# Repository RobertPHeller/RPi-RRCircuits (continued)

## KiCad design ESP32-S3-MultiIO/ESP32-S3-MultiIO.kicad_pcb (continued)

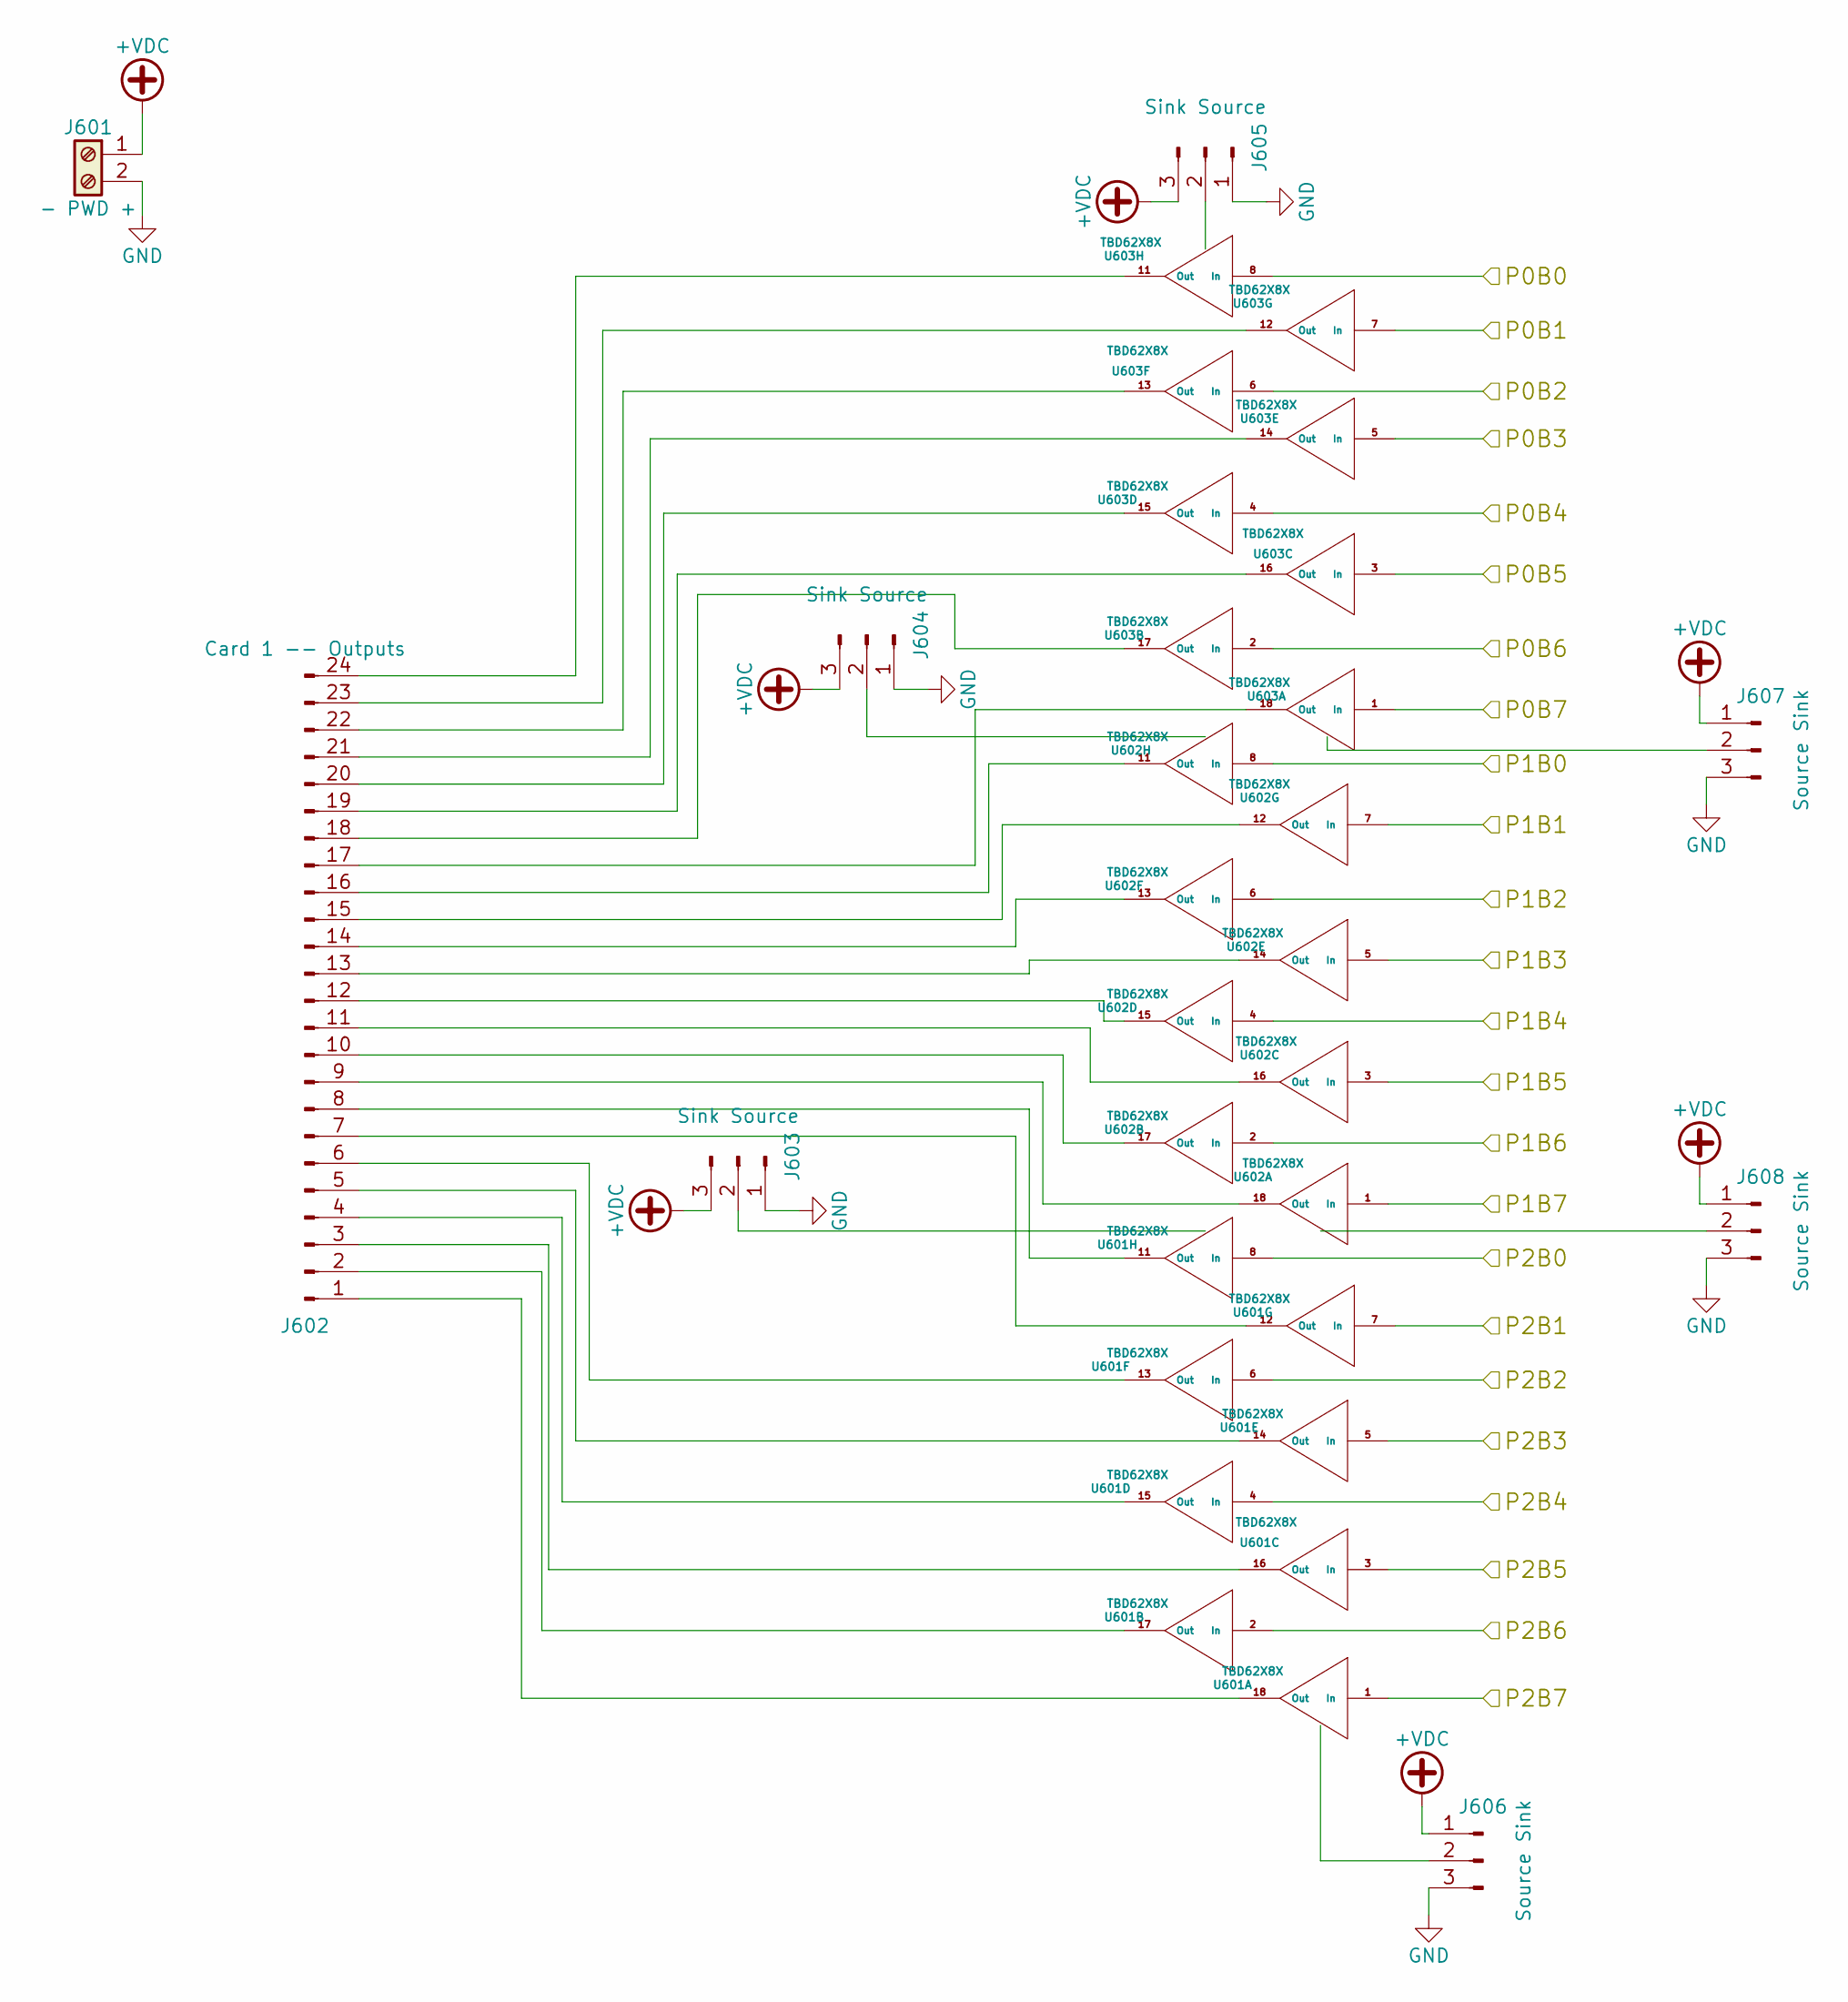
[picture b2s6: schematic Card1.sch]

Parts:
J601: - PWD +; TerminalBlock_Pheonix_MPT-2.54mm_2pol
J602: Card 1 -- Outputs; Molex_KK_396_01x24_3.96mm_RightAngle; Mouser Part Number 538-26-48-1242
J603, J604, J605: Sink Source; Pin_Header_Straight_1x03_Pitch2.54mm
J606, J607, J608: Source Sink; Pin_Header_Straight_1x03_Pitch2.54mm
U601, U602, U603: TBD62X8X; DIP-18_W7.62mm; Mouser Part Number 571-1-2199298-5

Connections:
+VDC: J601.1, J603.3, J604.3, J605.3, J606.1, J607.1, J608.1; also elsewhere on the board
/MCU/C1A0: U603.8 (In); also elsewhere on the board
/MCU/C1A1: U603.7 (In); also elsewhere on the board
/MCU/C1A2: U603.6 (In); also elsewhere on the board
/MCU/C1A3: U603.5 (In); also elsewhere on the board
/MCU/C1A4: U603.4 (In); also elsewhere on the board
/MCU/C1A5: U603.3 (In); also elsewhere on the board
/MCU/C1A6: U603.2 (In); also elsewhere on the board
/MCU/C1A7: U603.1 (In); also elsewhere on the board
/MCU/C1B0: U602.8 (In); also elsewhere on the board
/MCU/C1B1: U602.7 (In); also elsewhere on the board
/MCU/C1B2: U602.6 (In); also elsewhere on the board
/MCU/C1B3: U602.5 (In); also elsewhere on the board
/MCU/C1B4: U602.4 (In); also elsewhere on the board
/MCU/C1B5: U602.3 (In); also elsewhere on the board
/MCU/C1B6: U602.2 (In); also elsewhere on the board
/MCU/C1B7: U602.1 (In); also elsewhere on the board
/MCU/C1C0: U601.8 (In); also elsewhere on the board
/MCU/C1C1: U601.7 (In); also elsewhere on the board
/MCU/C1C2: U601.6 (In); also elsewhere on the board
/MCU/C1C3: U601.5 (In); also elsewhere on the board
/MCU/C1C4: U601.4 (In); also elsewhere on the board
/MCU/C1C5: U601.3 (In); also elsewhere on the board
/MCU/C1C6: U601.2 (In); also elsewhere on the board
/MCU/C1C7: U601.1 (In); also elsewhere on the board
GND: J601.2, J603.1, J604.1, J605.1, J606.3, J607.3, J608.3; also elsewhere on the board
unnamed: J602.1, U601.18 (Out)
unnamed: J602.2, U601.17 (Out)
unnamed: J602.3, U601.16 (Out)
unnamed: J602.4, U601.15 (Out)
unnamed: J602.5, U601.14 (Out)
unnamed: J602.6, U601.13 (Out)
unnamed: J602.7, U601.12 (Out)
unnamed: J602.8, U601.11 (Out)
unnamed: J602.9, U602.18 (Out)
unnamed: J602.10, U602.17 (Out)
unnamed: J602.11, U602.16 (Out)
unnamed: J602.12, U602.15 (Out)
unnamed: J602.13, U602.14 (Out)
unnamed: J602.14, U602.13 (Out)
unnamed: J602.15, U602.12 (Out)
unnamed: J602.16, U602.11 (Out)
unnamed: J602.17, U603.18 (Out)
unnamed: J602.18, U603.17 (Out)
unnamed: J602.19, U603.16 (Out)
unnamed: J602.20, U603.15 (Out)
unnamed: J602.21, U603.14 (Out)
unnamed: J602.22, U603.13 (Out)
unnamed: J602.23, U603.12 (Out)
unnamed: J602.24, U603.11 (Out)
unnamed: J603.2, U601.10 (OC)
unnamed: J604.2, U602.10 (OC)
unnamed: J605.2, U603.10 (OC)
unnamed: J606.2, U601.9 (IC)
unnamed: J607.2, U603.9 (IC)
unnamed: J608.2, U602.9 (IC)

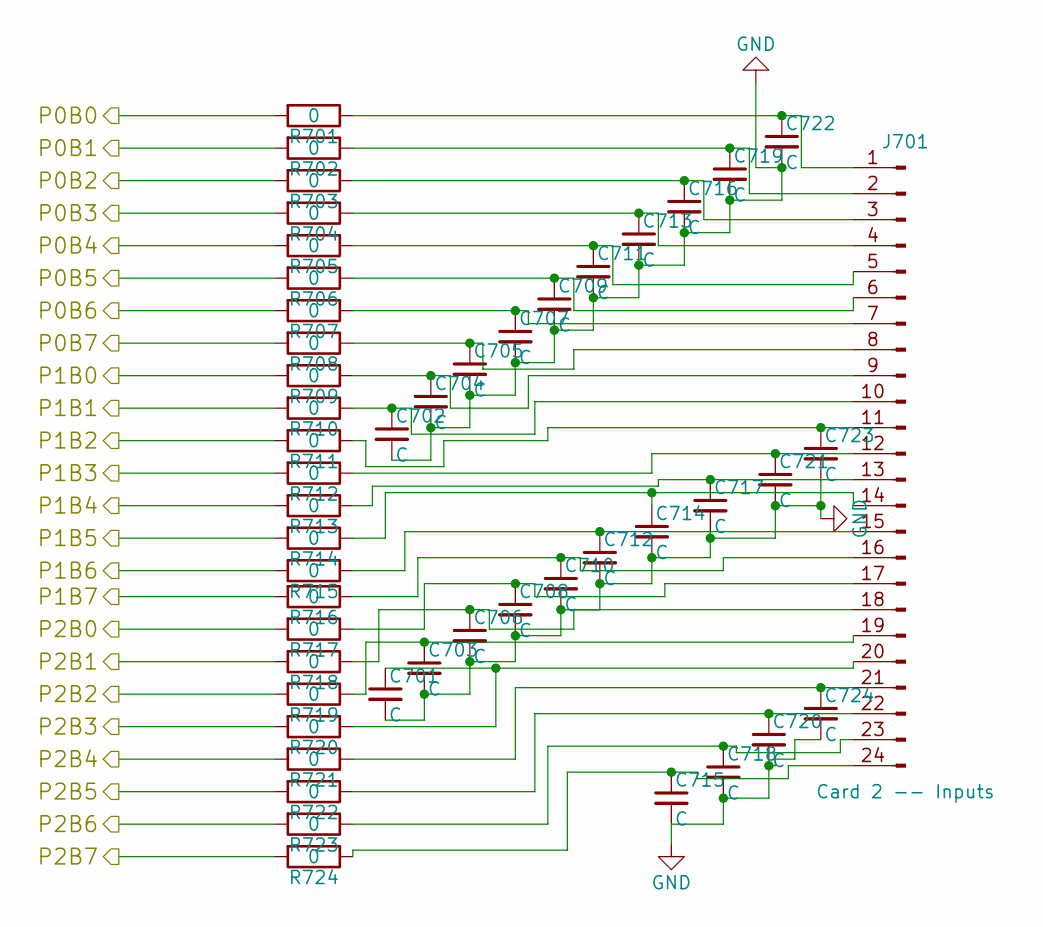
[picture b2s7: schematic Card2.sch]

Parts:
C701, C702, C703, C704, C705, C706, C707, C708, C709, C710, C711, C712, C713, C714, C715, C716, C717, C718, C719, C720, C721, C722, C723, C724: C; C_Disc_D3.8mm_W2.6mm_P2.50mm
J701: Card 2 -- Inputs; Molex_KK_396_01x24_3.96mm_RightAngle; Mouser Part Number 538-26-48-1242
R701, R702, R703, R704, R705, R706, R707, R708, R709, R710, R711, R712, R713, R714, R715, R716, R717, R718, R719, R720, R721, R722, R723, R724: 0; R_Axial_DIN0207_L6.3mm_D2.5mm_P10.16mm_Horizontal_WJumper

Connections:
/MCU/C2A0: R701.2; also elsewhere on the board
/MCU/C2A1: R702.2; also elsewhere on the board
/MCU/C2A2: R703.2; also elsewhere on the board
/MCU/C2A3: R704.2; also elsewhere on the board
/MCU/C2A4: R705.2; also elsewhere on the board
/MCU/C2A5: R706.2; also elsewhere on the board
/MCU/C2A6: R707.2; also elsewhere on the board
/MCU/C2A7: R708.2; also elsewhere on the board
/MCU/C2B0: R709.2; also elsewhere on the board
/MCU/C2B1: R710.2; also elsewhere on the board
/MCU/C2B2: R711.2; also elsewhere on the board
/MCU/C2B3: R712.2; also elsewhere on the board
/MCU/C2B4: R713.2; also elsewhere on the board
/MCU/C2B5: R714.2; also elsewhere on the board
/MCU/C2B6: R715.2; also elsewhere on the board
/MCU/C2B7: R716.2; also elsewhere on the board
/MCU/C2C0: R717.2; also elsewhere on the board
/MCU/C2C1: R718.2; also elsewhere on the board
/MCU/C2C2: R719.2; also elsewhere on the board
/MCU/C2C3: R720.2; also elsewhere on the board
/MCU/C2C4: R721.2; also elsewhere on the board
/MCU/C2C5: R722.2; also elsewhere on the board
/MCU/C2C6: R723.2; also elsewhere on the board
/MCU/C2C7: R724.2; also elsewhere on the board
GND: C701.2, C702.2, C703.2, C704.2, C705.2, C706.2, C707.2, C708.2, C709.2, C710.2, C711.2, C712.2, C713.2, C714.2, C715.2, C716.2, C717.2, C718.2, C719.2, C720.2, C721.2, C722.2, C723.2, C724.2; also elsewhere on the board
unnamed: C701.1, J701.20, R720.1
unnamed: C702.1, J701.10, R710.1
unnamed: C703.1, J701.19, R719.1
unnamed: C704.1, J701.9, R709.1
unnamed: C705.1, J701.8, R708.1
unnamed: C706.1, J701.18, R718.1
unnamed: C707.1, J701.7, R707.1
unnamed: C708.1, J701.17, R717.1
unnamed: C709.1, J701.6, R706.1
unnamed: C710.1, J701.16, R716.1
unnamed: C711.1, J701.5, R705.1
unnamed: C712.1, J701.15, R715.1
unnamed: C713.1, J701.4, R704.1
unnamed: C714.1, J701.14, R714.1
unnamed: C715.1, J701.24, R724.1
unnamed: C716.1, J701.3, R703.1
unnamed: C717.1, J701.13, R713.1
unnamed: C718.1, J701.23, R723.1
unnamed: C719.1, J701.2, R702.1
unnamed: C720.1, J701.22, R722.1
unnamed: C721.1, J701.12, R712.1
unnamed: C722.1, J701.1, R701.1
unnamed: C723.1, J701.11, R711.1
unnamed: C724.1, J701.21, R721.1

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
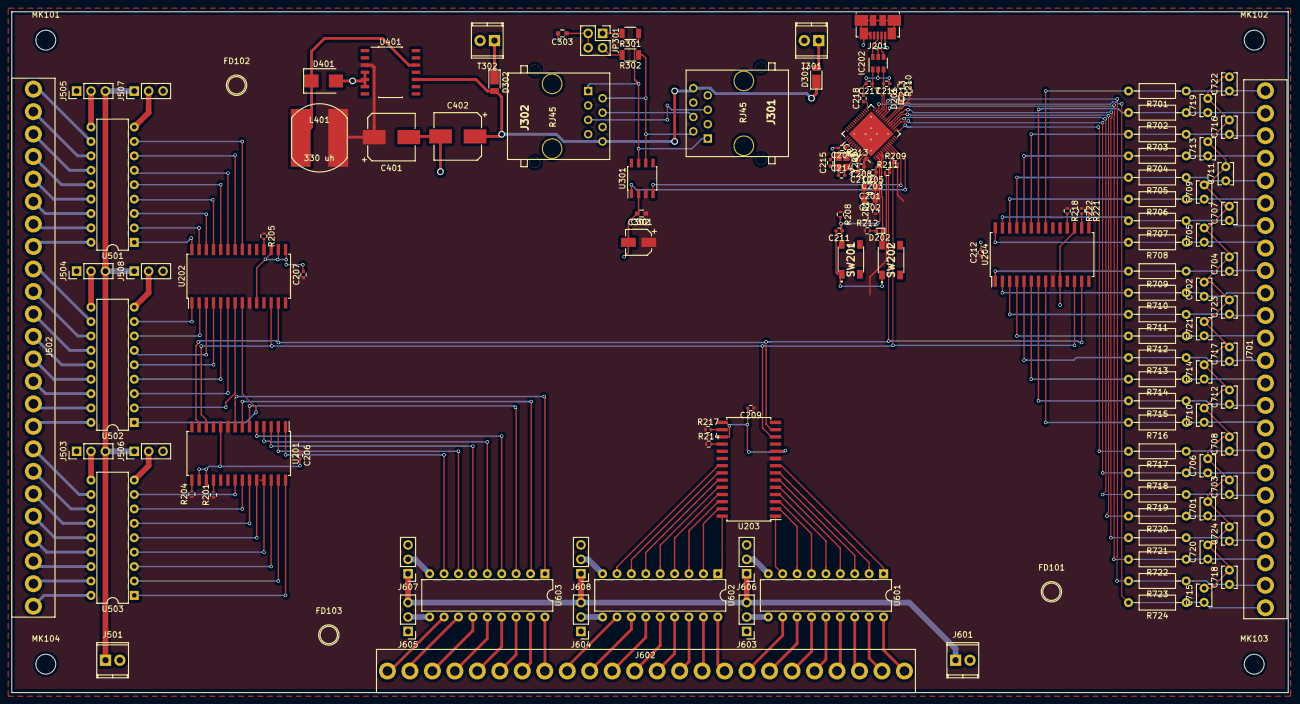
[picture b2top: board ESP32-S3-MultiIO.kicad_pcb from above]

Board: 2 copper layers, 225.0 x 120.0 mm, 141 parts (0 on the bottom side), 197 nets.

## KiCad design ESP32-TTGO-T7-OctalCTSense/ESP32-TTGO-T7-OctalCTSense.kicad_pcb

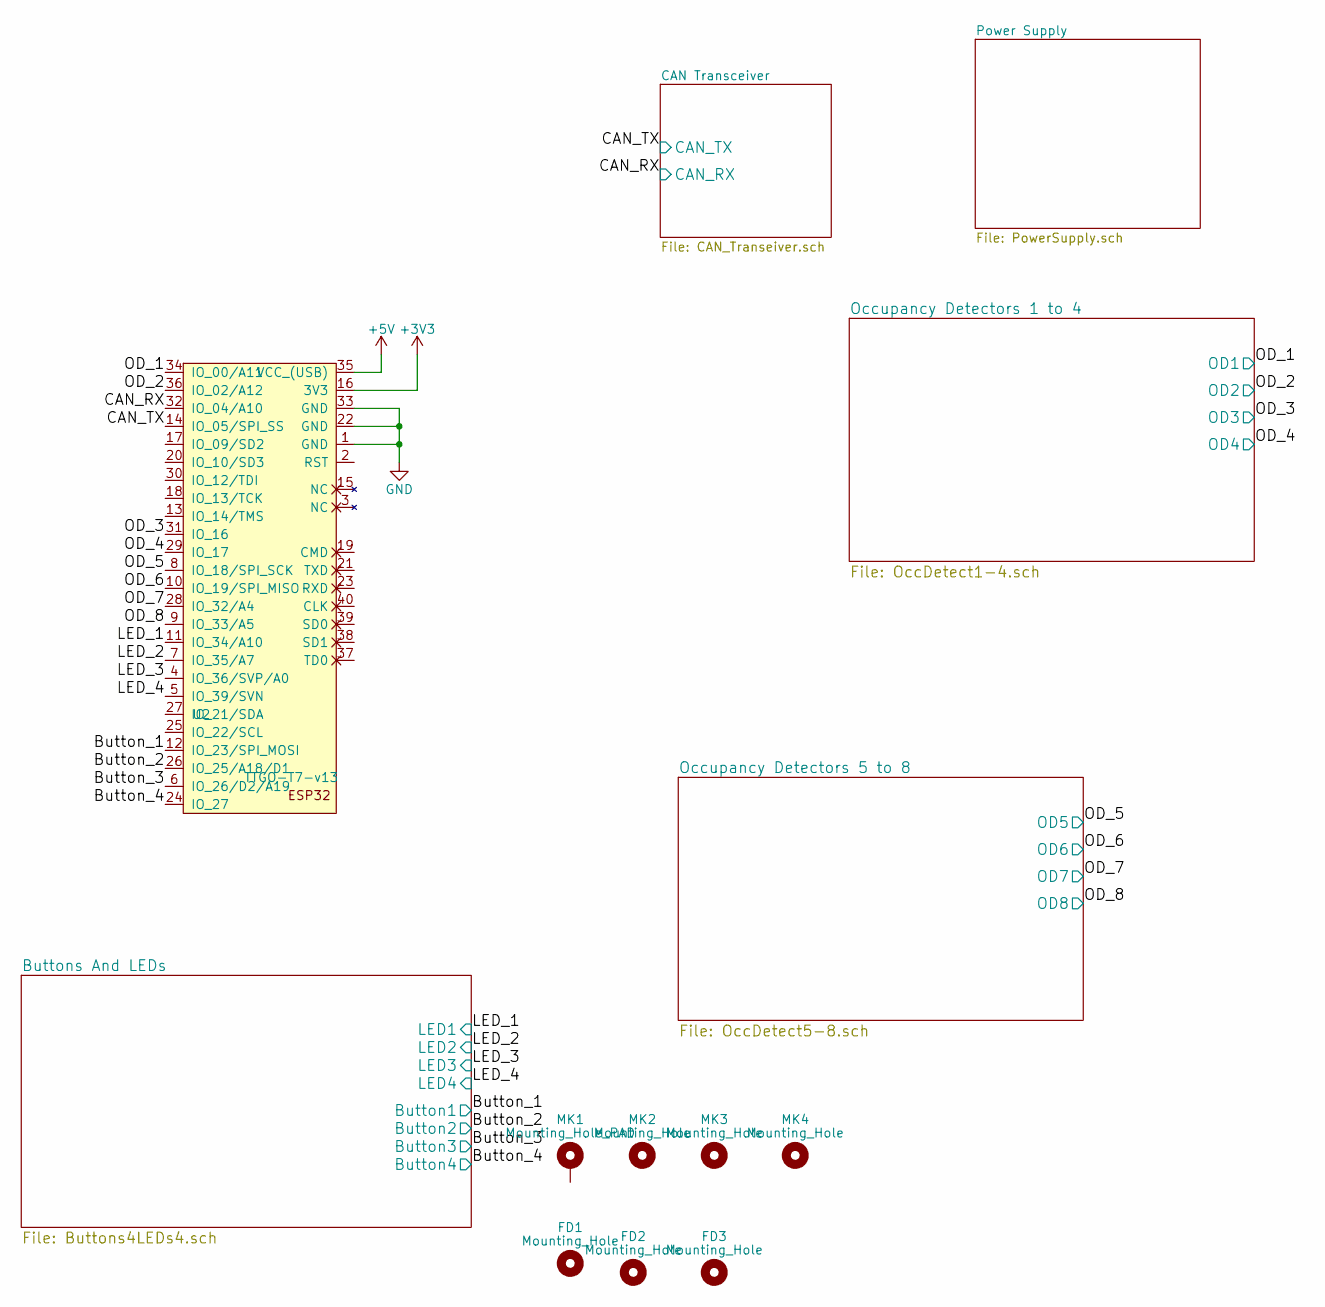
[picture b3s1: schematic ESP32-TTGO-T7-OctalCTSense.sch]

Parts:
FD1, FD2, FD3: Mounting_Hole; Fiducial_Modern_CopperTop
MK1: Mounting_Hole_PAD; MountingHole_3.2mm_M3_Pad_Via
MK2, MK3, MK4: Mounting_Hole; MountingHole_3.2mm_M3
U2: TTGO-T7-v13; ESP32_mini

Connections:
+5V: U2.35 (VCC_(USB)); also elsewhere on the board
/Button_1: U2.12 (IO_23/SPI_MOSI); also elsewhere on the board
/Button_2: U2.26 (IO_25/A18/D1); also elsewhere on the board
/Button_3: U2.6 (IO_26/D2/A19); also elsewhere on the board
/Button_4: U2.24 (IO_27); also elsewhere on the board
/CAN_RX: U2.32 (IO_04/A10); also elsewhere on the board
/CAN_TX: U2.14 (IO_05/SPI_SS); also elsewhere on the board
/LED_1: U2.11 (IO_34/A10); also elsewhere on the board
/LED_2: U2.7 (IO_35/A7); also elsewhere on the board
/LED_3: U2.4 (IO_36/SVP/A0); also elsewhere on the board
/LED_4: U2.5 (IO_39/SVN); also elsewhere on the board
/OD_1: U2.34 (IO_00/A11); also elsewhere on the board
/OD_2: U2.36 (IO_02/A12); also elsewhere on the board
/OD_3: U2.31 (IO_16); also elsewhere on the board
/OD_4: U2.29 (IO_17); also elsewhere on the board
/OD_5: U2.8 (IO_18/SPI_SCK); also elsewhere on the board
/OD_6: U2.10 (IO_19/SPI_MISO); also elsewhere on the board
/OD_7: U2.28 (IO_32/A4); also elsewhere on the board
/OD_8: U2.9 (IO_33/A5); also elsewhere on the board
GND: U2.1 (GND), U2.22 (GND), U2.33 (GND); also elsewhere on the board

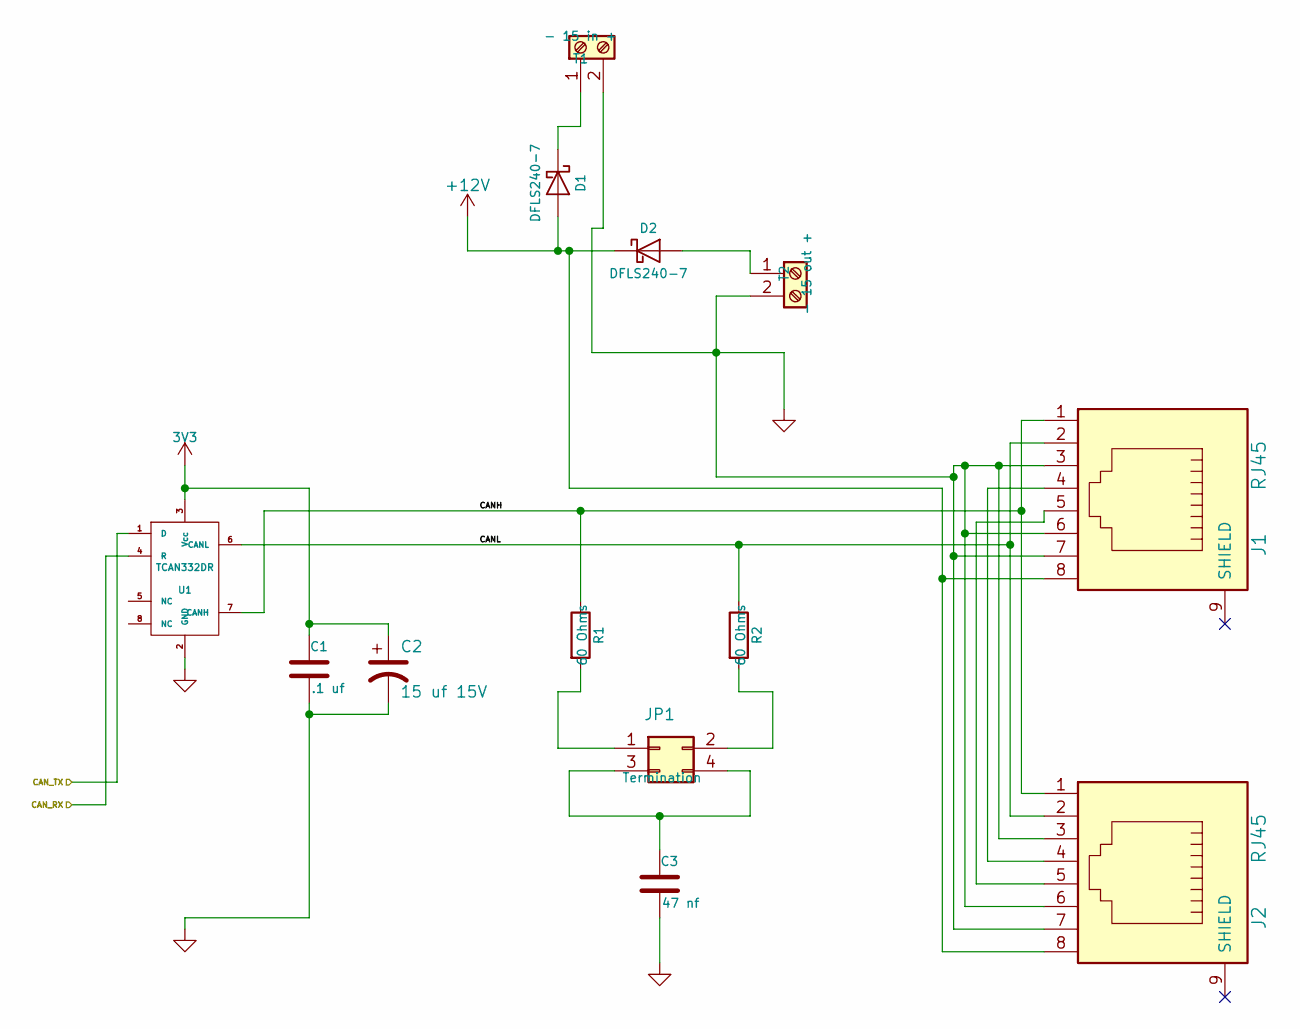
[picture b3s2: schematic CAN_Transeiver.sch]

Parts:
C1: .1 uf; C_0603; Mouser Part Number 710-885012206095
C2: 15 uf 15V; CP_Elec_4x5.7; Mouser Part Number 647-UUD1C150MCL
C3: 47 nf; C_0603; Mouser Part Number 710-885012206093
D1, D2: DFLS240-7; D_PowerDI-123; Mouser Part Number 621-DFLS240-7
J1, J2: RJ45; RJ45_8N-S; Mouser Part Number 710-615008144221
JP1: Termination; Pin_Header_Straight_2x02_Pitch2.54mm; Mouser Part Number 649-67997-404HLF
R1, R2: 60 Ohms; R_1206; Mouser Part Number 71-CRCW120660R0KNAIF
T1: - 15 in +; TerminalBlock_Pheonix_MPT-2.54mm_2pol; Mouser Part Number 651-1725656
T2: - 15 out +; TerminalBlock_Pheonix_MPT-2.54mm_2pol; Mouser Part Number 651-1725656
U1: TCAN332DR; SOIC-8_3.9x4.9mm_Pitch1.27mm; Mouser Part Number 595-TCAN332DR

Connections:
+12V: D1.2 (A), D2.1 (K), J1.8, J2.8; also elsewhere on the board
/CAN Transceiver/CANH: J1.1, J2.1, R1.1, U1.7 (CANH)
/CAN Transceiver/CANL: J1.2, J2.2, R2.1, U1.6 (CANL)
/CAN_RX: U1.4 (R); also elsewhere on the board
/CAN_TX: U1.1 (D); also elsewhere on the board
GND: C1.2, C2.2, C3.2, J1.3, J1.6, J1.7, J2.3, J2.6, J2.7, T1.2, T2.2, U1.2 (GND); also elsewhere on the board
unnamed: C3.1, JP1.3, JP1.4
unnamed: D1.1 (K), T1.1
unnamed: D2.2 (A), T2.1
unnamed: J1.4, J2.4
unnamed: J1.5, J2.5
unnamed: JP1.1, R1.2
unnamed: JP1.2, R2.2

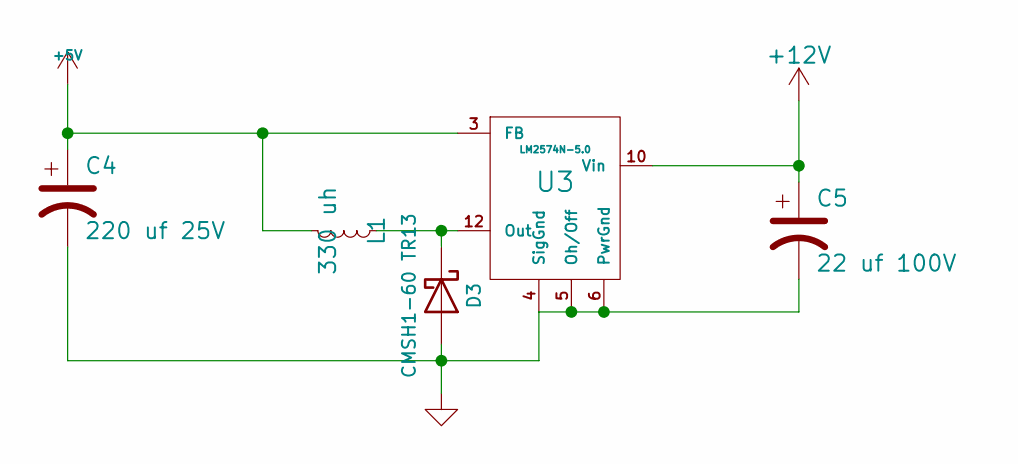
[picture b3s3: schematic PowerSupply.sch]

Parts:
C4: 220 uf 25V; CP_Elec_8x10; Mouser Part Number 647-UWT1E221MNL1GS
C5: 22 uf 100V; CP_Elec_8x10; Mouser Part Number 647-UUX2A220MNL6GS
D3: CMSH1-60 TR13; D_SMB; Mouser Part Number 610-CMSH1-60TR13
L1: 330 uh; SRN1060; Mouser Part Number 652-SRN1060-331M
U3: LM2574N-5.0; SOIC-14_7.4x8.7mm_Pitch1.27mm; Mouser Part Number 926-LM2574N-5.0/NOPB

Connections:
+5V: C4.1, L1.2, U3.3 (FB); also elsewhere on the board
+12V: C5.1, U3.10 (Vin); also elsewhere on the board
GND: C4.2, C5.2, D3.2 (A), U3.4 (SigGnd), U3.5 (Oh/Off), U3.6 (PwrGnd); also elsewhere on the board
unnamed: D3.1 (K), L1.1, U3.12 (Out)

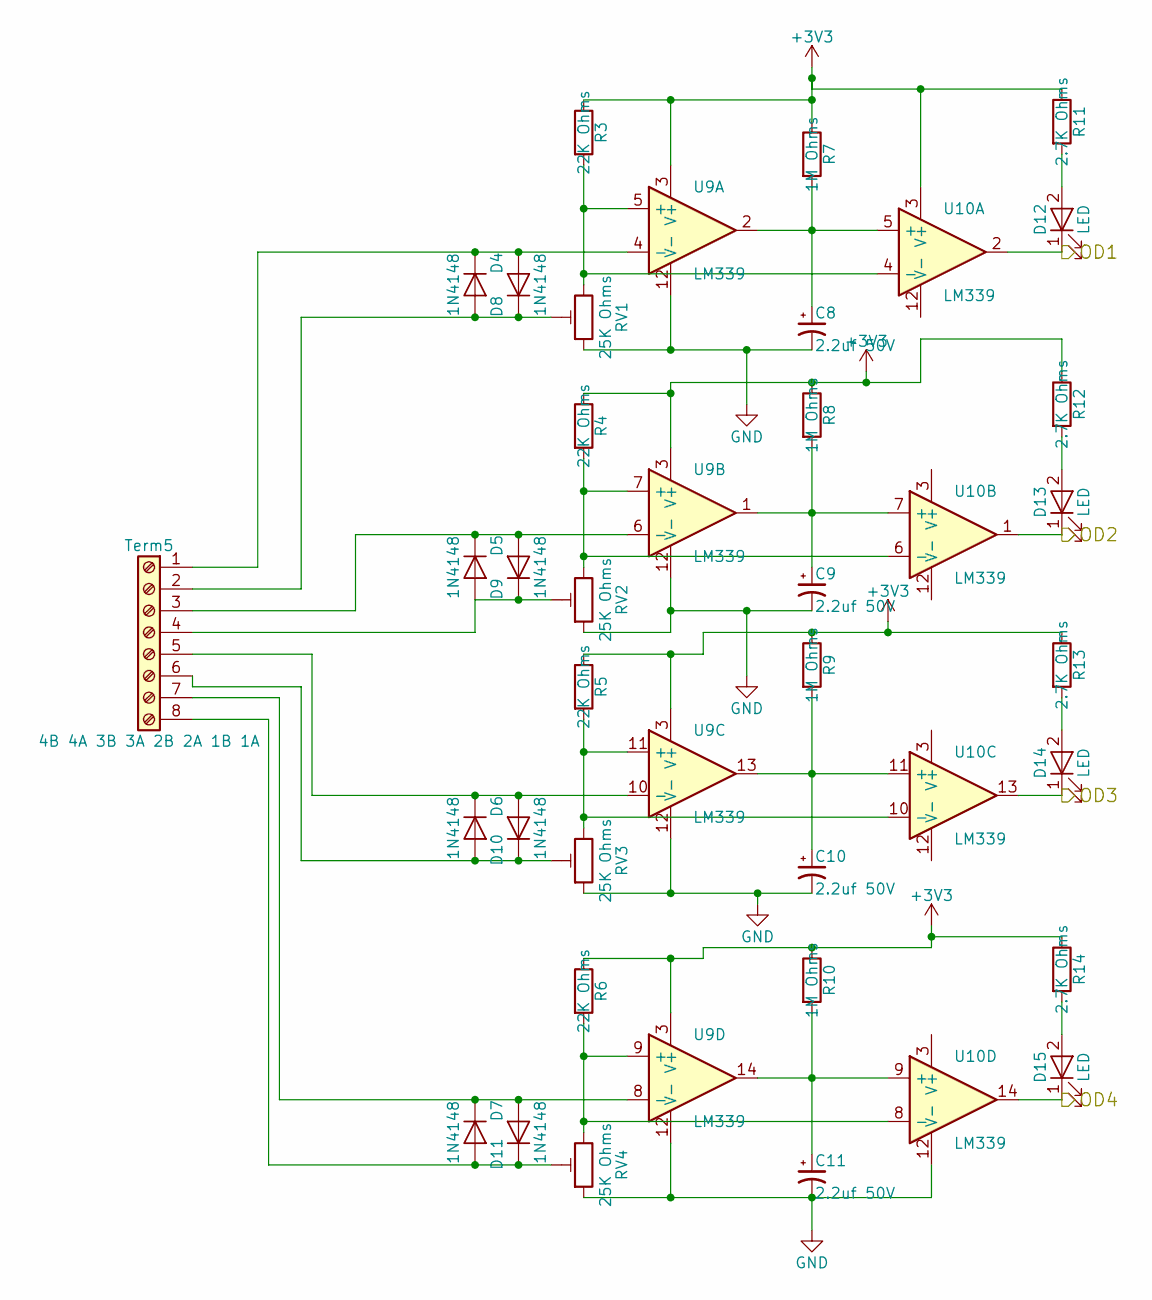
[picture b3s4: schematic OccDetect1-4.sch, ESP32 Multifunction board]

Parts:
C8, C9, C10, C11: 2.2uf 50V; CP_Elec_4x5.7; Mouser Part Number 710-865080140002
D4, D5, D6, D7, D8, D9, D10, D11: 1N4148; D_SOD-123; Mouser Part Number 750-1N4148WS-HF
D12, D13, D14, D15: LED; LED_0603; Mouser Part Number 710-150060SS55040
R3, R4, R5, R6: 22K Ohms; R_0603; Mouser Part Number 71-RCG060322K0JNEA
R7, R8, R9, R10: 1M Ohms; R_0603; Mouser Part Number 71-CRCW06031M00JNEAC
R11, R12, R13, R14: 2.7K Ohms; R_0603; Mouser Part Number 71-CRCW06032K70JNEAC
RV1, RV2, RV3, RV4: 25K Ohms; Potentiometer_Trimmer_Bourns_3214J; Mouser Part Number 652-3314J-1-253E
Term5: 4B 4A 3B 3A 2B 2A 1B 1A; TerminalBlock_Pheonix_MPT-2.54mm_8pol; Mouser Part Number 651-1725711
U9, U10: LM339; SOIC-14_3.9x8.7mm_Pitch1.27mm

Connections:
/OD_1: D12.1 (K), U10.2; also elsewhere on the board
/OD_2: D13.1 (K), U10.1; also elsewhere on the board
/OD_3: D14.1 (K), U10.13; also elsewhere on the board
/OD_4: D15.1 (K), U10.14; also elsewhere on the board
GND: C8.2, C9.2, C10.2, C11.2, RV1.1, RV2.1, RV3.1, RV4.1, U9.12 (V-), U10.12 (V-); also elsewhere on the board
unnamed: C8.1, R7.2, U9.2, U10.5 (+)
unnamed: C9.1, R8.2, U9.1, U10.7 (+)
unnamed: C10.1, R9.2, U9.13, U10.11 (+)
unnamed: C11.1, R10.2, U9.14, U10.9 (+)
unnamed: D4.1 (K), D8.2 (A), Term5.1, U9.4 (-)
unnamed: D4.2 (A), D8.1 (K), RV1.2, Term5.2
unnamed: D5.1 (K), D9.2 (A), Term5.3, U9.6 (-)
unnamed: D5.2 (A), D9.1 (K), RV2.2, Term5.4
unnamed: D6.2 (A), D10.1 (K), RV3.2, Term5.6
unnamed: D6.1 (K), D10.2 (A), Term5.5, U9.10 (-)
unnamed: D7.2 (A), D11.1 (K), RV4.2, Term5.8
unnamed: D7.1 (K), D11.2 (A), Term5.7, U9.8 (-)
unnamed: D12.2 (A), R11.2
unnamed: D13.2 (A), R12.2
unnamed: D14.2 (A), R13.2
unnamed: D15.2 (A), R14.2
unnamed: R3.2, RV1.3, U9.5 (+), U10.4 (-)
unnamed: R4.2, RV2.3, U9.7 (+), U10.6 (-)
unnamed: R5.2, RV3.3, U9.11 (+), U10.10 (-)
unnamed: R6.2, RV4.3, U9.9 (+), U10.8 (-)

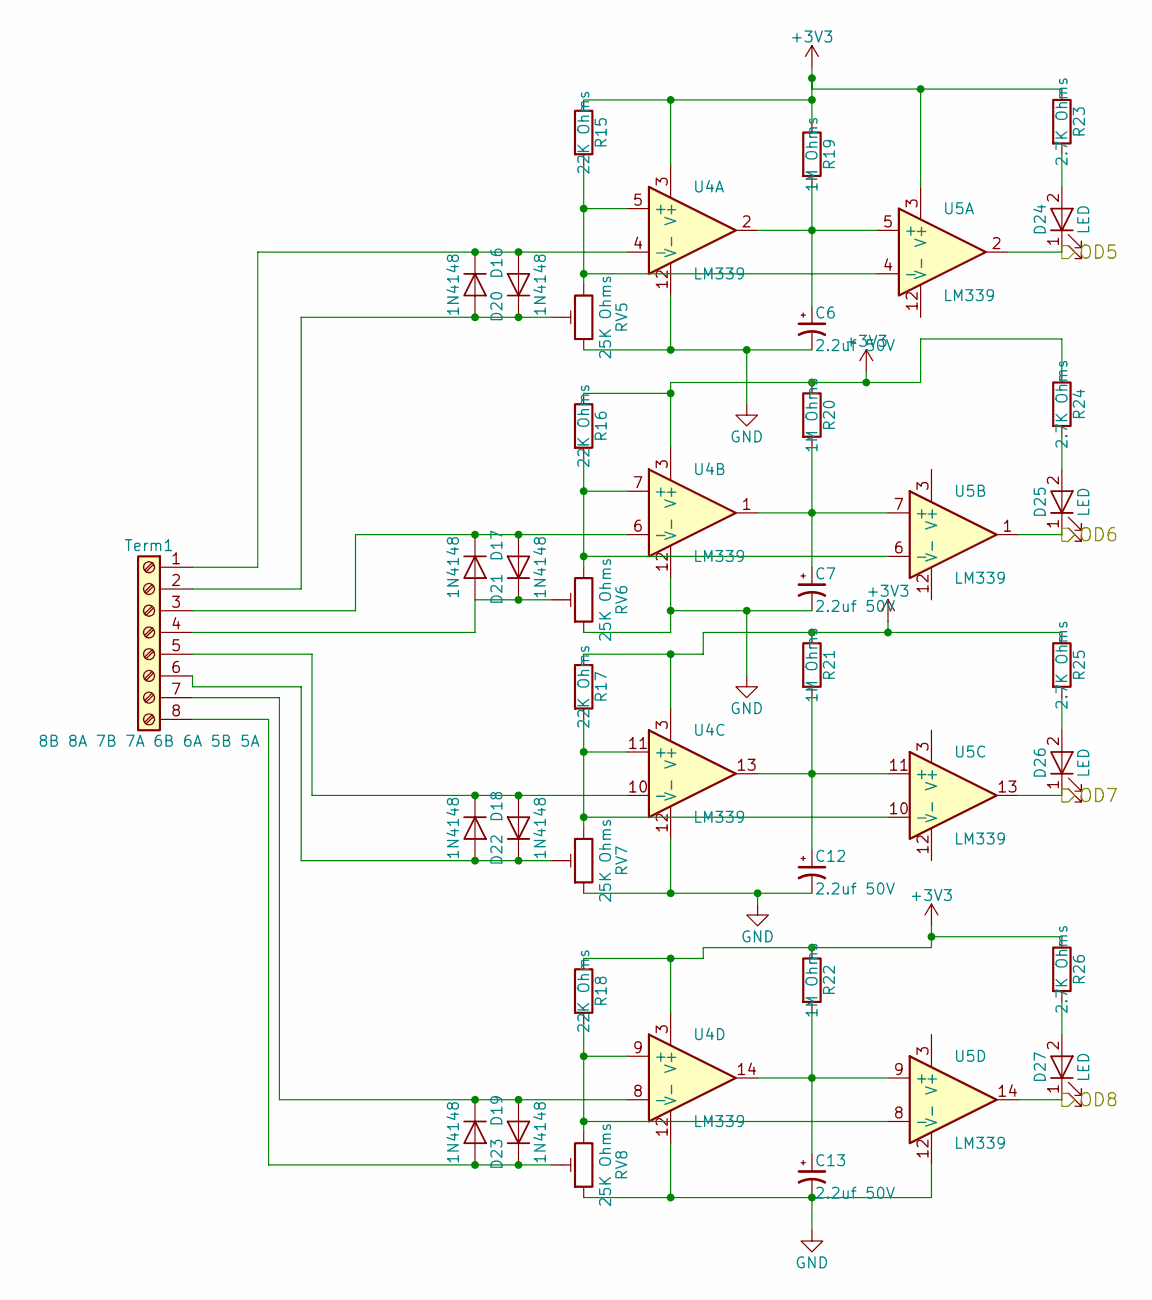
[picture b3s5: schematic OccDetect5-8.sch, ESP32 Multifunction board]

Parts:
C6, C7, C12, C13: 2.2uf 50V; CP_Elec_4x5.7; Mouser Part Number 710-865080140002
D16, D17, D18, D19, D20, D21, D22, D23: 1N4148; D_SOD-123; Mouser Part Number 750-1N4148WS-HF
D24, D25, D26, D27: LED; LED_0603; Mouser Part Number 710-150060SS55040
R15, R16, R17, R18: 22K Ohms; R_0603; Mouser Part Number 71-RCG060322K0JNEA
R19, R20, R21, R22: 1M Ohms; R_0603; Mouser Part Number 71-CRCW06031M00JNEAC
R23, R24, R25, R26: 2.7K Ohms; R_0603; Mouser Part Number 71-CRCW06032K70JNEAC
RV5, RV6, RV7, RV8: 25K Ohms; Potentiometer_Trimmer_Bourns_3214J; Mouser Part Number 652-3314J-1-253E
Term1: 8B 8A 7B 7A 6B 6A 5B 5A; TerminalBlock_Pheonix_MPT-2.54mm_8pol; Mouser Part Number 651-1725711
U4, U5: LM339; SOIC-14_3.9x8.7mm_Pitch1.27mm

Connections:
/OD_5: D24.1 (K), U5.2; also elsewhere on the board
/OD_6: D25.1 (K), U5.1; also elsewhere on the board
/OD_7: D26.1 (K), U5.13; also elsewhere on the board
/OD_8: D27.1 (K), U5.14; also elsewhere on the board
GND: C6.2, C7.2, C12.2, C13.2, RV5.1, RV6.1, RV7.1, RV8.1, U4.12 (V-), U5.12 (V-); also elsewhere on the board
unnamed: C6.1, R19.2, U4.2, U5.5 (+)
unnamed: C7.1, R20.2, U4.1, U5.7 (+)
unnamed: C12.1, R21.2, U4.13, U5.11 (+)
unnamed: C13.1, R22.2, U4.14, U5.9 (+)
unnamed: D16.1 (K), D20.2 (A), Term1.1, U4.4 (-)
unnamed: D16.2 (A), D20.1 (K), RV5.2, Term1.2
unnamed: D17.1 (K), D21.2 (A), Term1.3, U4.6 (-)
unnamed: D17.2 (A), D21.1 (K), RV6.2, Term1.4
unnamed: D18.1 (K), D22.2 (A), Term1.5, U4.10 (-)
unnamed: D18.2 (A), D22.1 (K), RV7.2, Term1.6
unnamed: D19.1 (K), D23.2 (A), Term1.7, U4.8 (-)
unnamed: D19.2 (A), D23.1 (K), RV8.2, Term1.8
unnamed: D24.2 (A), R23.2
unnamed: D25.2 (A), R24.2
unnamed: D26.2 (A), R25.2
unnamed: D27.2 (A), R26.2
unnamed: R15.2, RV5.3, U4.5 (+), U5.4 (-)
unnamed: R16.2, RV6.3, U4.7 (+), U5.6 (-)
unnamed: R17.2, RV7.3, U4.11 (+), U5.10 (-)
unnamed: R18.2, RV8.3, U4.9 (+), U5.8 (-)
